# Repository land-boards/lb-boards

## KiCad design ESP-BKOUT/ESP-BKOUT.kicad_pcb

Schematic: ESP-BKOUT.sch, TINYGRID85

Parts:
C1, C3, C4, C5: 0.1uF; R_0805_HandSoldering
C2, C6, C7: 22uF; R_1210_HandSoldering
J1: DCJ0202; JACK_2.1MM
MTG1, MTG2, MTG3, MTG4: CONN_1; MTG-4-40
P1: CONN_01X04; Pin_Header_Straight_1x04
P2: CONN_01X10; Pin_Header_Straight_1x10
P3: CONN_01X08; Pin_Header_Straight_1x08
P4: CONN_01X02; Pin_Header_Straight_1x02
U1: TXS0108; SOG20
U2: AP1117-3.3V; SOT-223
U3: arduino_mini
U4: AZ1117-5.0V; SOT-223
U5: ESP8266-ESP-01

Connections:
+3V3: C5.1, C6.1, U1.2 (VCCA(LV)), U1.10 (OE), U2.2 (VO), U2.4 (VO), U5.3 (CH_PD), U5.7 (3V3)
+5V: C2.1, C3.1, C4.1, C7.1, P1.2, P2.9, P3.7, U1.19 (VCCB(HV)), U2.3 (VIN), U3.12 (5V), U4.2 (VO), U4.4 (VO)
+9V: C1.1, J1.1, U3.15 (Vin), U4.3 (VIN)
/A0: P2.1, U3.4 (A0)
/A1: P2.2, U3.5 (A1)
/A2: P2.3, U3.6 (A2)
/A3: P2.4, U3.7 (A3)
/A6: P2.7, U3.10 (A6)
/A7: P2.8, U3.11 (A7)
/ARDRXD: P1.3, U1.18 (G2), U3.26 (D8)
/ARDTXD: P1.4, U1.20 (B1), U3.27 (#D9)
/D4: P3.4, U3.22 (D4)
/D5: P3.3, U3.23 (#D5)
/D6: P3.2, U3.24 (#D6)
/D7: P3.1, U3.25 (D7)
/ESPRXD: U1.1 (A1), U5.8 (RX)
/ESPTXD: U1.3 (A2), U5.1 (TX)
/SCL: P2.6, U3.9 (A5(SCL))
/SDA: P2.5, U3.8 (A4(SDA))
GND: C1.2, C2.2, C3.2, C4.2, C5.2, C6.2, C7.2, J1.2, J1.3, P1.1, P2.10, P3.8, P4.2, U1.11 (GND), U2.1 (GND), U3.14 (GND), U3.19 (GND), U4.1 (GND), U5.2 (GND)
unnamed: P3.5, U3.21 ((int3)#D3)
unnamed: P3.6, U3.20 ((int2)D2)
unnamed: P4.1, U5.6 (GPIO0)

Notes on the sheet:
VOLTAGE REGULATOR

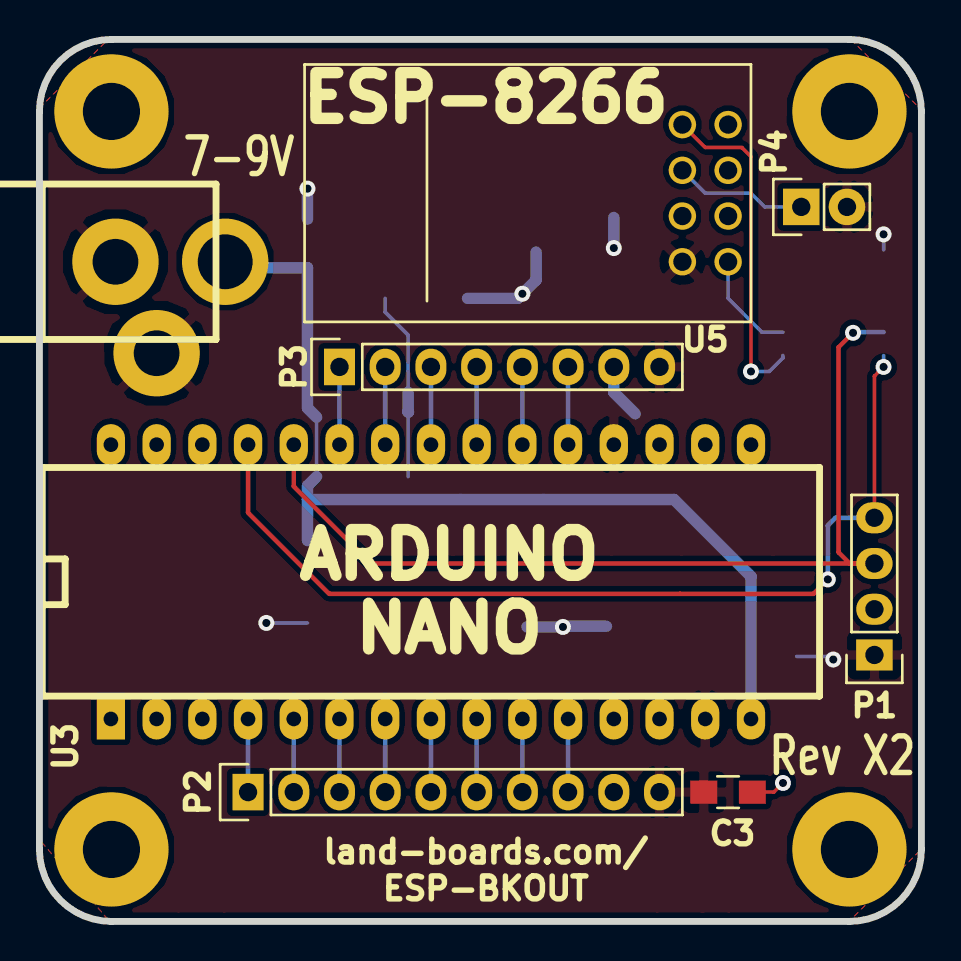
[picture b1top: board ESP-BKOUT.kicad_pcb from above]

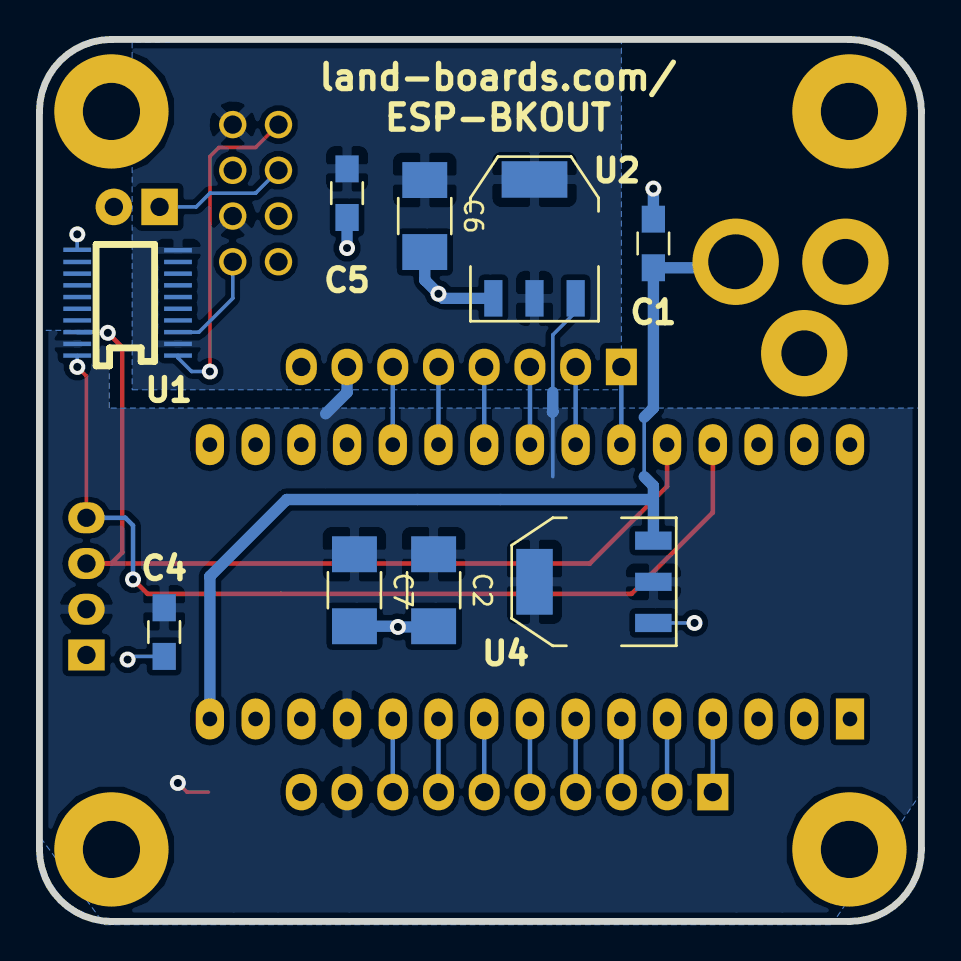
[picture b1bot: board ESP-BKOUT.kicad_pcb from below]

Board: 2 copper layers, 49.0 x 49.0 mm, 21 parts (9 on the bottom side), 23 nets.

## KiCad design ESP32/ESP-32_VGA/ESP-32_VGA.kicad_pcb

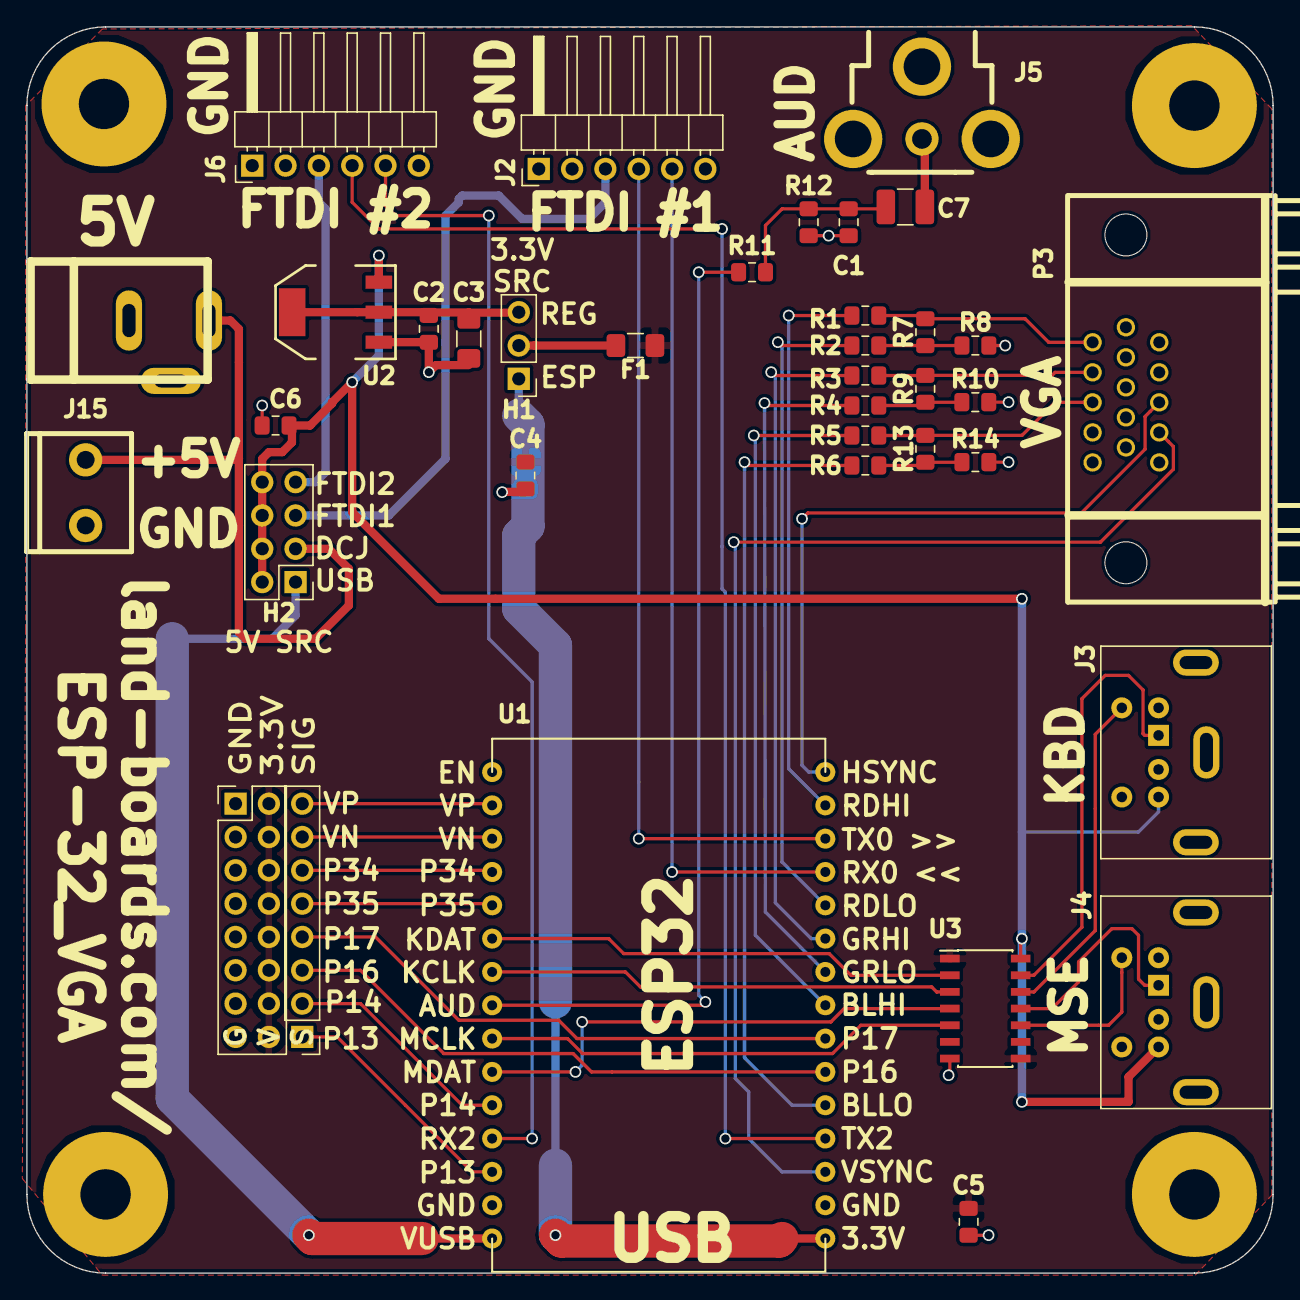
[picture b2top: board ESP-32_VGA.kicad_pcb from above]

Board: 2 copper layers, 95.0 x 95.0 mm, 42 parts (0 on the bottom side), 47 nets.

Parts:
C1, C2, C4, C5, C6: 0.1uF; C_0805_2012Metric_Pad1.15x1.40mm_HandSolder
C3: 10uF; C_1206_3216Metric_Pad1.42x1.75mm_HandSolder
C7: CP1; C_1210_3225Metric_Pad1.42x2.65mm_HandSolder
F1: Polyfuse_Small; Fuse_1206_3216Metric_Pad1.42x1.75mm_HandSolder
H1: Conn_01x03; PinHeader_1x03_P2.54mm_Vertical
H2: Conn_02x04_Odd_Even; PinHeader_2x04_P2.54mm_Vertical
J1: DCJ0202; DCJ-NEW-Slotted
J2, J6: FTDI; PinHeader_1x06_P2.54mm_Horizontal
J3, J4: PS2_DIN6; Connector_Mini-DIN_Female_6Pin_2rows
J5: RCA-JACK; RCA
J15: Conn_01x02; TB2-5MM
MTG1, MTG2, MTG3: MTG_HOLE; MTG-6-32
MTG?1: MTG_HOLE; MTG-6-32
P2: Conn_02x08_Odd_Even; PinHeader_2x08_P2.54mm_Vertical
P3: VGA; DB_15F-VGA-fixed
P4: Conn_01x08; PinHeader_1x08_P2.54mm_Vertical
R1: 1K; R_0805_2012Metric_Pad1.15x1.40mm_HandSolder
R2, R4, R6: 680; R_0805_2012Metric_Pad1.15x1.40mm_HandSolder
R3, R5, R7, R8, R9, R10, R13, R14: 470; R_0805_2012Metric_Pad1.15x1.40mm_HandSolder
R11: 270; R_0805_2012Metric_Pad1.15x1.40mm_HandSolder
R12: 150; R_0805_2012Metric_Pad1.15x1.40mm_HandSolder
TEST1: COUPON; TEST_BLK-REAR
U1: ESP32; ESP32_EXP
U2: AP1117; SOT223
U3: TXS0104; SOIC-14_3.9x8.7mm_P1.27mm

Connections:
+3V3: C4.1, C5.1, F1.1, P2.2, P2.4, P2.6, P2.8, P2.10, P2.12, P2.14, P2.16, U3.1, U3.8
+5V: C6.1, H2.2, H2.4, H2.6, H2.8, J3.4, J4.4, U2.3, U3.14
/AUDIO: R11.2, U1.23
/BLUHI: R5.2, U1.8
/BLULO: R6.2, U1.5
/DCIN: H2.3, J1.1, J15.2
/ESP3V: H1.1, U1.1
/FTDI5V0: H2.5, J2.3
/FTDI5V2: H2.7, J6.3
/GP13: P4.1, U1.28
/GP14: P4.2, U1.26
/GP16: P4.3, U1.6
/GP17: P4.4, U1.7
/GP34: P4.6, U1.19
/GP35: P4.5, U1.20
/GRNHI: R3.2, U1.10
/GRNLO: R4.2, U1.9
/HSYNC: P3.13, U1.15
/KBCLK: U1.22, U3.3
/KBDAT: U1.21, U3.2
/MSECLK: U1.24, U3.5
/MSEDAT: U1.25, U3.4
/REDHI: R1.2, U1.14
/REDLO: R2.2, U1.11
/RX0: J2.5, U1.12
/RX2: J6.5, U1.27
/TX0: J2.4, U1.13
/TX2: J6.4, U1.4
/VN: P4.7, U1.18
/VO3: C2.1, C3.1, H1.3, U2.2, U2.4
/VP: P4.8, U1.17
/VSYNC: P3.14, U1.3
/VUSB: H2.1, U1.30
GND: C1.2, C2.2, C3.2, C4.2, C5.2, C6.2, J1.2, J1.3, J2.1, J3.3, J4.3, J5.1, J5.2, J5.3, J6.1, J15.1, P2.1, P2.3, P2.5, P2.7, P2.9, P2.11, P2.13, P2.15, P3.5, P3.6, P3.7, P3.8, P3.10, R8.1, R10.1, R12.1, R14.1, U1.2, U1.29, U2.1, U3.7
unnamed: C1.1, C7.1, R11.1, R12.2
unnamed: C7.2, J5.4
unnamed: F1.2, H1.2
unnamed: J3.1, U3.13
unnamed: J3.5, U3.12
unnamed: J4.1, U3.11
unnamed: J4.5, U3.10
unnamed: P3.1, R1.1, R7.2
unnamed: P3.2, R3.1, R9.2
unnamed: P3.3, R5.1, R13.2
unnamed: R2.1, R7.1, R8.2
unnamed: R4.1, R9.1, R10.2
unnamed: R6.1, R13.1, R14.2

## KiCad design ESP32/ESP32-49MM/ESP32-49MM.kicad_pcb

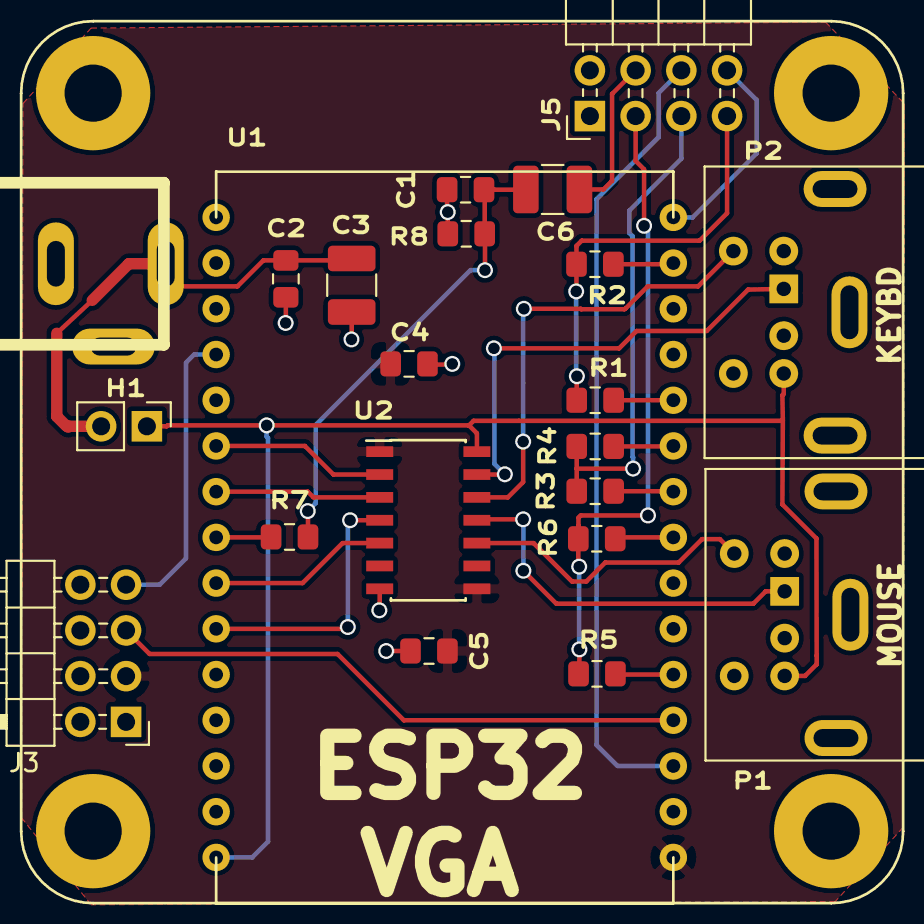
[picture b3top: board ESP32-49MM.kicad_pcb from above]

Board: 2 copper layers, 24 parts (0 on the bottom side), 28 nets.

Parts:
BRD1: COUPON; BD-49X49
C1, C2, C4, C5: 0.1uF; C_0805_2012Metric_Pad1.15x1.40mm_HandSolder
C3, C6: 10uF; C_1210_3225Metric_Pad1.42x2.65mm_HandSolder
H1: Conn_01x02; PinHeader_1x02_P2.54mm_Vertical
J1: DCJ0202; DCJ-NEW-Slotted
J3: Header, Vert, 2x4; PinHeader_2x04_P2.54mm_Horizontal
J5: Conn_02x04_Odd_Even; PinHeader_2x04_P2.54mm_Horizontal
P1: MINI-DIN6, PS2 (GRN); Connector_Mini-DIN_Female_6Pin_2rows
P2: MINI-DIN6, PS2 (PURP); Connector_Mini-DIN_Female_6Pin_2rows
R1, R3, R5: 422; R_0805_2012Metric_Pad1.15x1.40mm_HandSolder
R2, R4, R6: 845; R_0805_2012Metric_Pad1.15x1.40mm_HandSolder
R7: 270; R_0805_2012Metric_Pad1.15x1.40mm_HandSolder
R8: 150; R_0805_2012Metric_Pad1.15x1.40mm_HandSolder
TEST1: COUPON; TEST_BLK-REAR
U1: ESP32 MODULE; ESP32_EXP
U2: TXS0104EDR; SOIC-14_3.9x8.7mm_P1.27mm

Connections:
+3V3: C4.1, C5.1, J3.3, U1.1, U2.1, U2.8
+5V: H1.1, P1.4, P2.4, U1.30, U2.14
/AOUT: C6.2, J5.4
/AUDIO: R7.2, U1.23
/BLUHI: R5.2, U1.5
/BLULO: R6.2, U1.8
/GRNHI: R3.2, U1.9
/GRNLO: R4.2, U1.10
/HSYNC: J5.8, U1.15
/KBCLK: U1.22, U2.3
/KBDAT: U1.21, U2.2
/MSECLK: U1.24, U2.5
/MSEDAT: U1.25, U2.4
/REDHI: R1.2, U1.11
/REDLO: R2.2, U1.14
/RX2: J3.7, U1.19
/TX2: J3.5, U1.4
/VSYNC: J5.6, U1.3
GND: C1.2, C2.2, C3.2, C4.2, C5.2, J1.2, J1.3, J3.1, J5.1, J5.2, P1.3, P2.3, R8.1, U1.2, U1.29, U2.7
unnamed: C1.1, C6.1, R7.1, R8.2
unnamed: C2.1, C3.1, H1.2, J1.1
unnamed: J5.3, R5.1, R6.1
unnamed: J5.5, R3.1, R4.1
unnamed: J5.7, R1.1, R2.1
unnamed: P1.1, U2.11
unnamed: P1.5, U2.10
unnamed: P2.1, U2.13
unnamed: P2.5, U2.12

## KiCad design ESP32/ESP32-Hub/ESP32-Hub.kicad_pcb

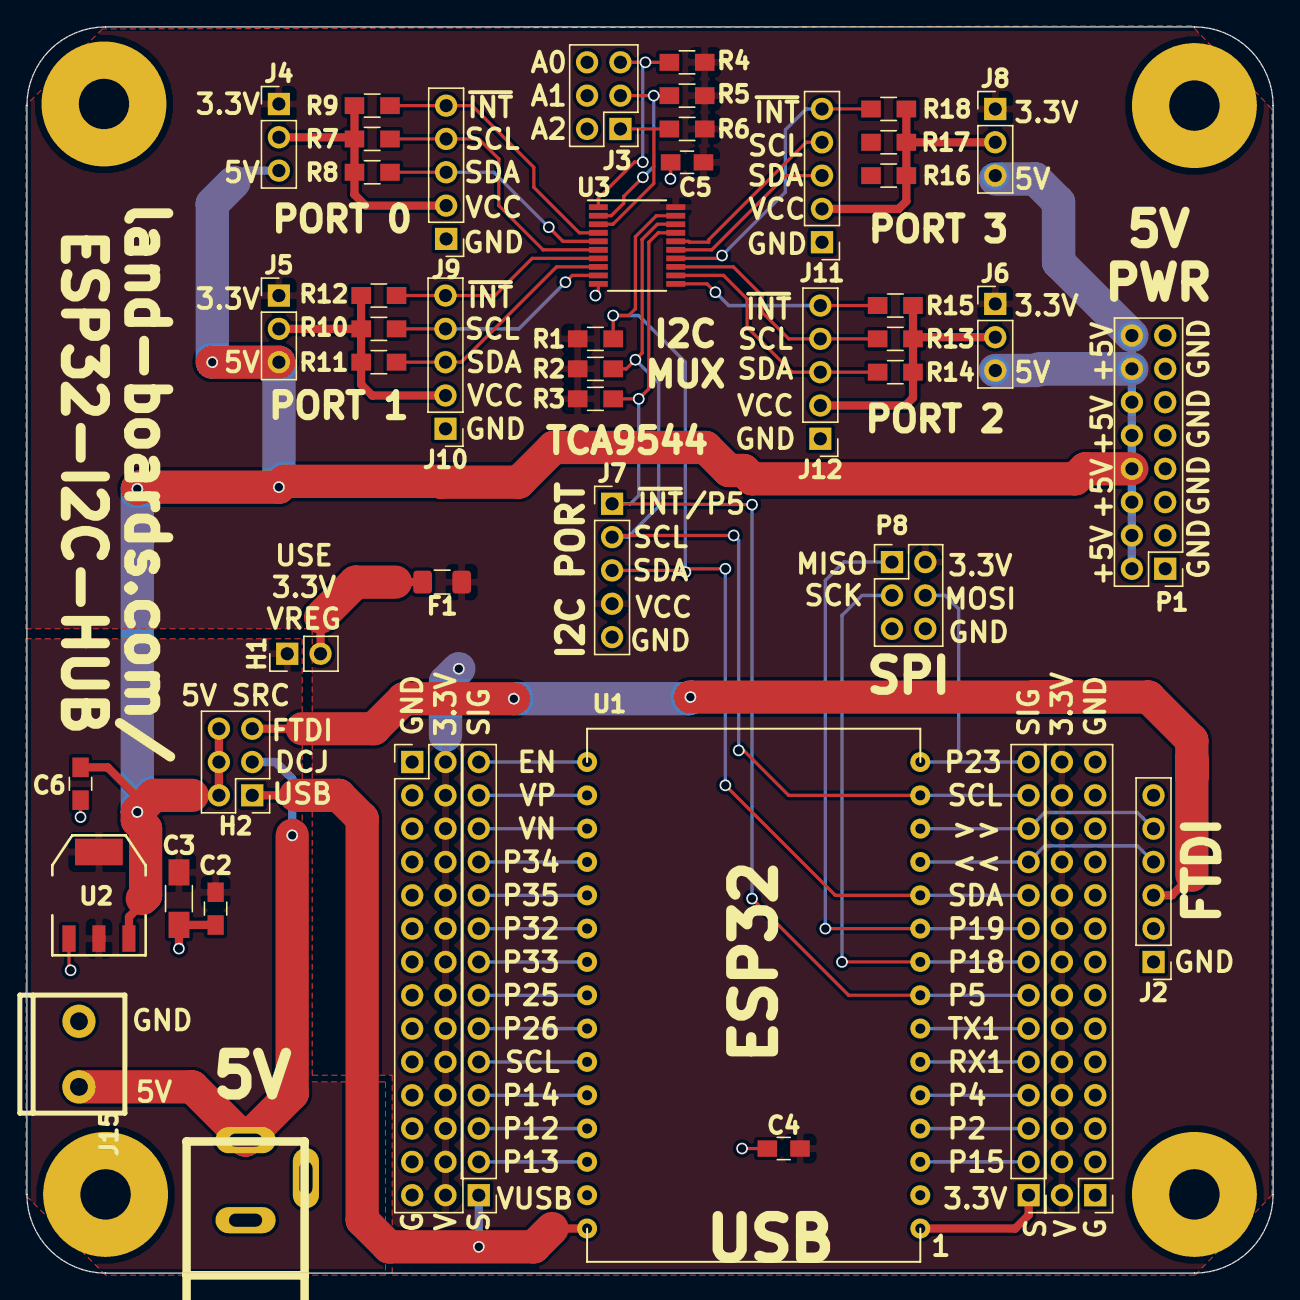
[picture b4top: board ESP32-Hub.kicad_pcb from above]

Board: 2 copper layers, 95.0 x 95.0 mm, 52 parts (0 on the bottom side), 54 nets.

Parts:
C2, C4, C5, C6: 0.1uF; C_0805_HandSoldering
C3: 10uF; C_1206_HandSoldering
F1: Polyfuse, 1A (1206); Fuse_1206_3216Metric_Pad1.42x1.75mm_HandSolder
H1: Header, Rt ang, 1x2; PinHeader_1x02_P2.54mm_Vertical
H2: Header, Vert, 2x3; PinHeader_2x03_P2.54mm_Vertical
J1: DC Pwr Jack, 5.5mmx2.1mm; DCJ-NEW-Slotted
J2: Header, 1x6, Rt Ang, (FTDI); Pin_Header_Straight_1x06_Pitch2.54mm
J3: Header, Vert, 2x3; Pin_Header_Straight_2x03_Pitch2.54mm
J4, J5, J6, J8: Header, Strt, 1x3; Pin_Header_Straight_1x03_Pitch2.54mm
J7, J9, J10, J11, J12: Header, Strt, 1x5; Pin_Header_Straight_1x05_Pitch2.54mm
J15: Term Blk, 5mm, 1x2; TB2-5MM
MTG1, MTG2, MTG3, MTG4: MTG_HOLE; MTG-6-32
P1: Header, Vert, 2x8; Pin_Header_Straight_2x08_Pitch2.54mm
P2, P11: Header, Vert, 2x14; Pin_Header_Straight_2x14_Pitch2.54mm
P8: Header, Vert, 2x3; Pin_Header_Straight_2x03_Pitch2.54mm
P12, P13: Header, Vert, 1x14; Pin_Header_Straight_1x14_Pitch2.54mm
R1, R3, R7, R8, R10, R11, R13, R14, R16, R17: 2.2K; R_0805_HandSoldering
R2, R4, R5, R6, R9, R12, R15, R18: 10K; R_0805_HandSoldering
U1: ESP32 MODULE; ESP32_EXP
U2: AP1117E33G-13 (3.3V); SOT223
U3: PCA9544APWR; TSSOP-20_4.4x6.5mm_Pitch0.65mm

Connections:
+3V3: C4.1, C5.1, F1.1, J4.1, J5.1, J6.1, J7.4, J8.1, P2.2, P2.4, P2.6, P2.8, P2.10, P2.12, P2.14, P2.16, P2.18, P2.20, P2.22, P2.24, P2.26, P2.28, P8.2, P11.2, P11.4, P11.6, P11.8, P11.10, P11.12, P11.14, P11.16, P11.18, P11.20, P11.22, P11.24, P11.26, P11.28, R1.1, R2.1, R3.1, R4.1, R5.1, R6.1, U3.20
+5V: C6.1, H2.2, H2.4, H2.6, J4.3, J5.3, J6.3, J8.3, P1.2, P1.4, P1.6, P1.8, P1.10, P1.12, P1.14, P1.16, U2.3
/A0: J3.5, R4.2, U3.1
/A1: J3.3, R5.2, U3.2
/A2: J3.1, R6.2, U3.3
/DCIN: H2.3, J1.1, J15.1
/EN: P13.14, U1.16
/FTDI5V: H2.5, J2.3
/GP2: P12.3, U1.4
/GP4: P12.4, U1.5
/GP5: J7.1, P12.7, R3.2, U1.8, U3.17
/GP12: P13.3, U1.27
/GP13: P13.2, U1.28
/GP14: P13.4, U1.26
/GP15: P12.2, U1.3
/GP18: P8.3, P12.8, U1.9
/GP19: P8.1, P12.9, U1.10
/GP23: P8.4, P12.14, U1.15
/GP25: P13.7, U1.23
/GP26: P13.6, U1.24
/GP27: P13.5, U1.25
/GP32: P13.9, U1.21
/GP33: P13.8, U1.22
/GP34: P13.11, U1.19
/GP35: P13.10, U1.20
/INT0: J9.5, R9.2, U3.4
/INT1: J10.5, R12.2, U3.7
/INT2: J12.5, R15.2, U3.11
/INT3: J11.5, R18.2, U3.14
/RX0: J2.4, P12.11, U1.12
/RX2: P12.5, U1.6
/SC0: J9.4, R7.2, U3.6
/SC1: J10.4, R10.2, U3.9
/SC2: J12.4, R13.2, U3.13
/SC3: J11.4, U3.16
/SD0: J9.3, R8.2, U3.5
/SD1: J10.3, R11.2, U3.8
/SD2: J12.3, R14.2, U3.12
/SD3: J11.3, U3.15
/STM_SCL: J7.2, P12.13, R2.2, U1.14, U3.18
/STM_SDA: J7.3, P12.10, R1.2, U1.11, U3.19
/TX0: J2.5, P12.12, U1.13
/TX2: P12.6, U1.7
/VN: P13.12, U1.18
/VO3: C2.1, C3.1, H1.1, U2.2, U2.4
/VP: P13.13, U1.17
/VUSB: H2.1, P13.1, U1.30
GND: C2.2, C3.2, C4.2, C5.2, C6.2, J1.2, J1.3, J2.1, J3.2, J3.4, J3.6, J7.5, J9.1, J10.1, J11.1, J12.1, J15.2, P1.1, P1.3, P1.5, P1.7, P1.9, P1.11, P1.13, P1.15, P2.1, P2.3, P2.5, P2.7, P2.9, P2.11, P2.13, P2.15, P2.17, P2.19, P2.21, P2.23, P2.25, P2.27, P8.6, P11.1, P11.3, P11.5, P11.7, P11.9, P11.11, P11.13, P11.15, P11.17, P11.19, P11.21, P11.23, P11.25, P11.27, U1.2, U1.29, U2.1, U3.10
unnamed: F1.2, H1.2
unnamed: J4.2, J9.2, R7.1, R8.1, R9.1
unnamed: J5.2, J10.2, R10.1, R11.1, R12.1
unnamed: J8.2, J11.2, R16.1, R17.1, R18.1
unnamed: J6.2, J12.2, R13.1, R14.1, R15.1
unnamed: P12.1, U1.1

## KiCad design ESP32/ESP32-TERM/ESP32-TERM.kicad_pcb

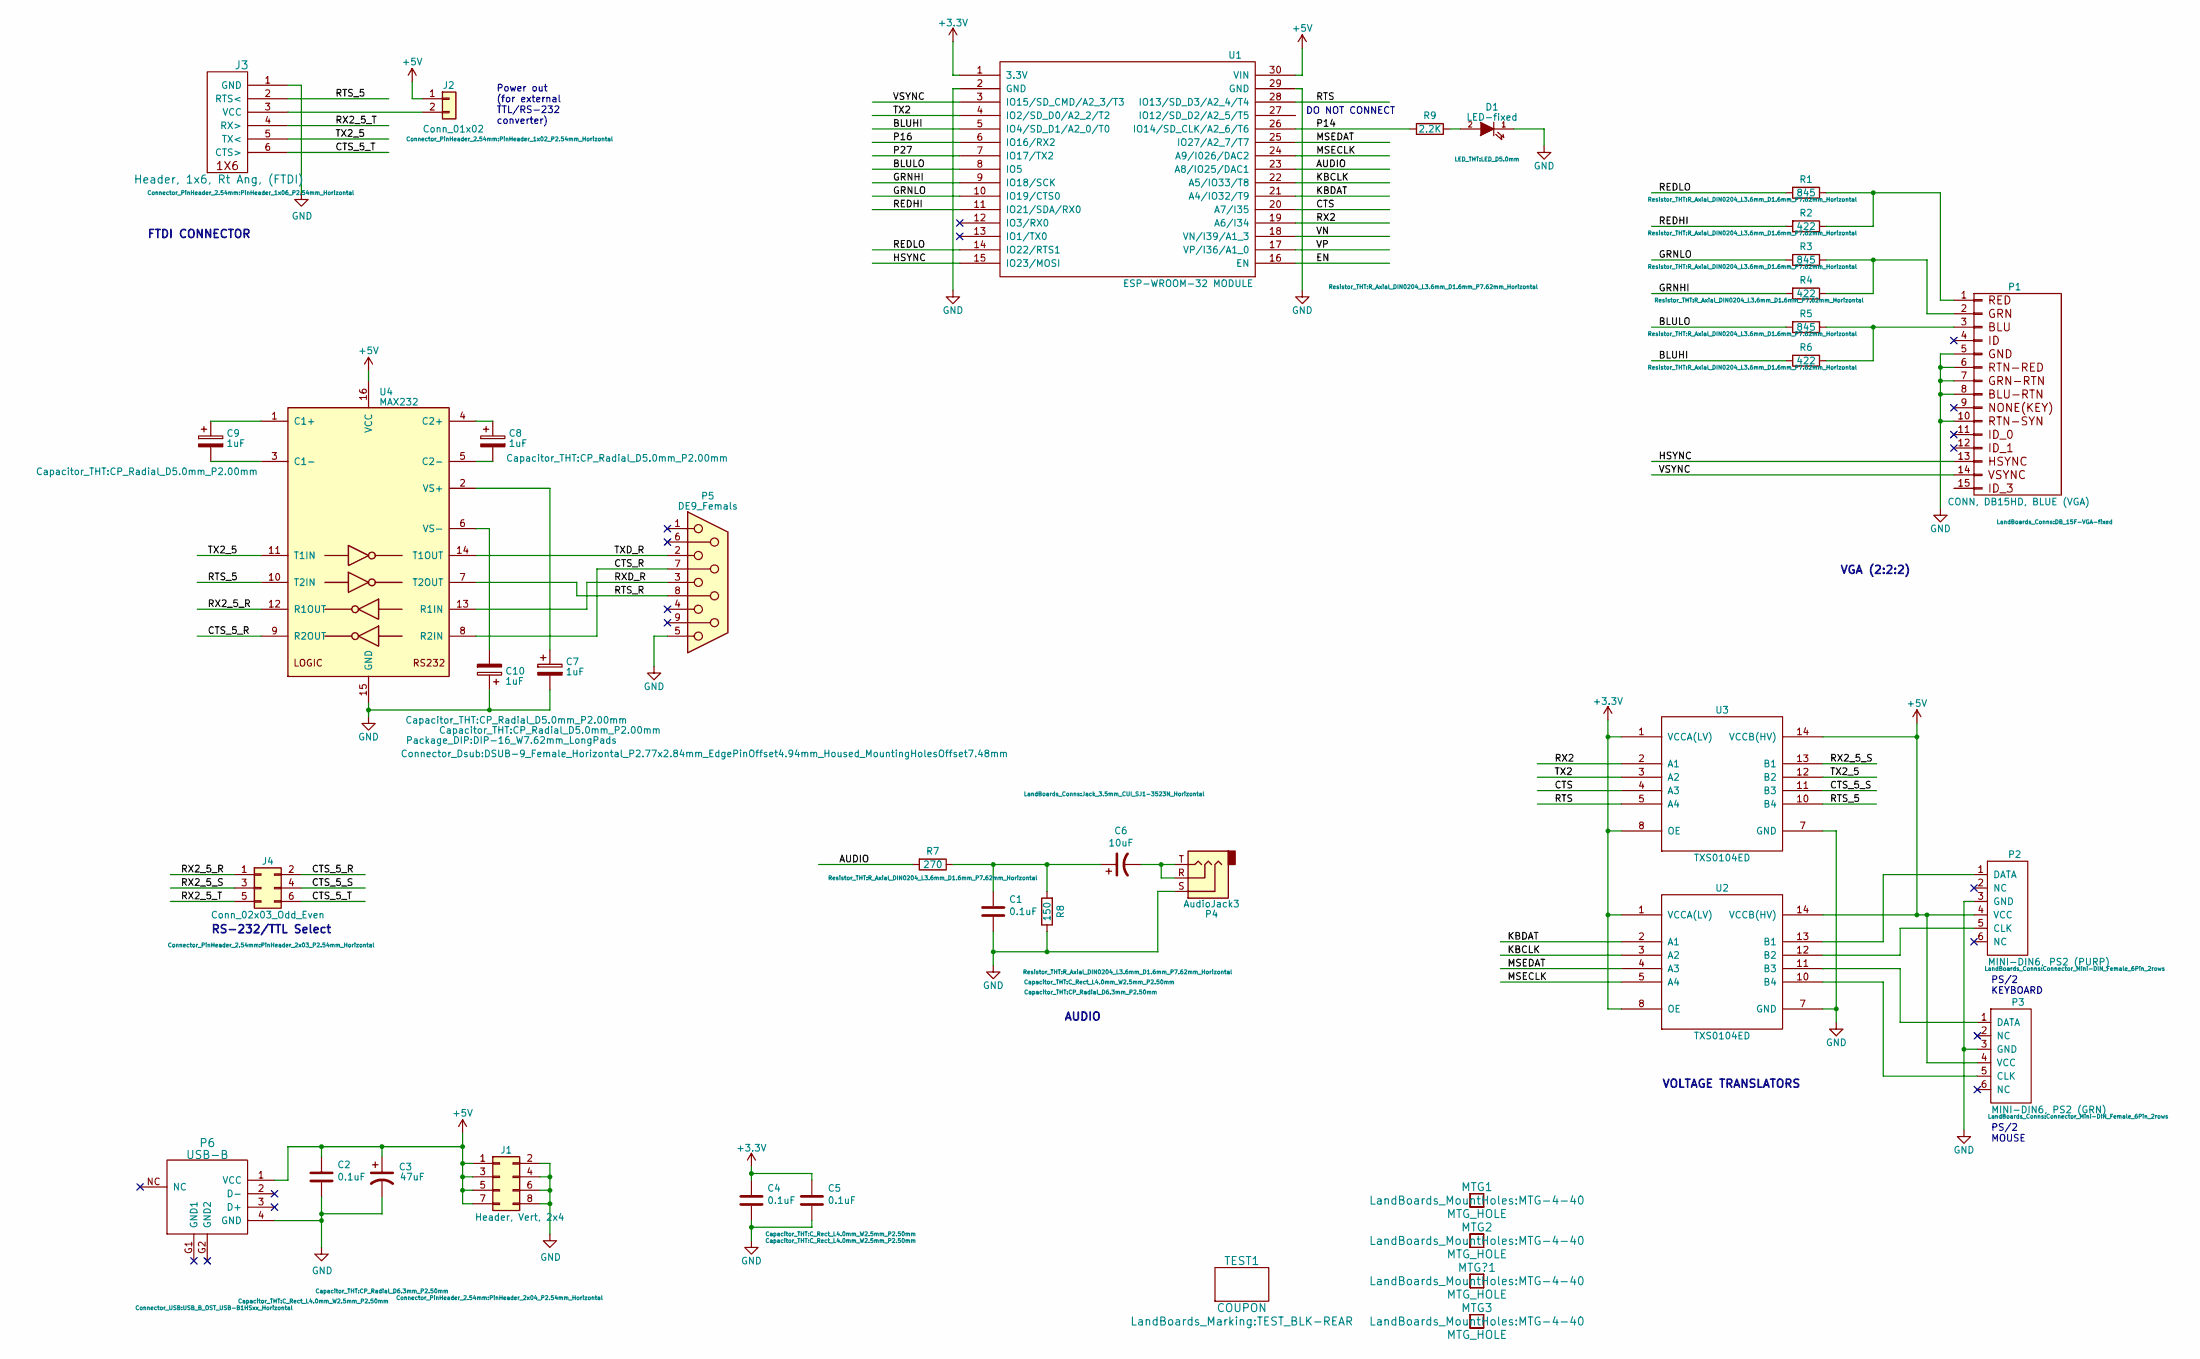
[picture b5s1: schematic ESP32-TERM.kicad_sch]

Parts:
C1, C2, C4, C5: 0.1uF; C_Rect_L4.0mm_W2.5mm_P2.50mm
C3: 47uF; CP_Radial_D6.3mm_P2.50mm
C6: 10uF; CP_Radial_D6.3mm_P2.50mm
C7, C8, C9, C10: 1uF; CP_Radial_D5.0mm_P2.00mm
D1: LED-fixed; LED_D5.0mm
J1: Header, Vert, 2x4; PinHeader_2x04_P2.54mm_Horizontal
J2: Conn_01x02; PinHeader_1x02_P2.54mm_Horizontal
J3: Header, 1x6, Rt Ang, (FTDI); PinHeader_1x06_P2.54mm_Horizontal
J4: Conn_02x03_Odd_Even; PinHeader_2x03_P2.54mm_Horizontal
MTG1, MTG2, MTG3: MTG_HOLE; MTG-4-40
MTG?1: MTG_HOLE; MTG-4-40
P1: CONN, DB15HD, BLUE (VGA); DB_15F-VGA-fixed
P2: MINI-DIN6, PS2 (PURP); Connector_Mini-DIN_Female_6Pin_2rows
P3: MINI-DIN6, PS2 (GRN); Connector_Mini-DIN_Female_6Pin_2rows
P4: AudioJack3; Jack_3.5mm_CUI_SJ1-3523N_Horizontal
P5: DE9_Femals; DSUB-9_Female_Horizontal_P2.77x2.84mm_EdgePinOffset4.94mm_H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
P6: USB-B; USB_B_OST_USB-B1HSxx_Horizontal
R1, R3, R5: 845; R_Axial_DIN0204_L3.6mm_D1.6mm_P7.62mm_Horizontal
R2, R4, R6: 422; R_Axial_DIN0204_L3.6mm_D1.6mm_P7.62mm_Horizontal
R7: 270; R_Axial_DIN0204_L3.6mm_D1.6mm_P7.62mm_Horizontal
R8: 150; R_Axial_DIN0204_L3.6mm_D1.6mm_P7.62mm_Horizontal
R9: 2.2K; R_Axial_DIN0204_L3.6mm_D1.6mm_P7.62mm_Horizontal
TEST1: COUPON; TEST_BLK-REAR
U1: ESP-WROOM-32 MODULE; ESP32_EXP
U2, U3: TXS0104ED; SOIC-14_3.9x8.7mm_P1.27mm
U4: MAX232; DIP-16_W7.62mm_LongPads

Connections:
+3V3: C4.1, C5.1, U1.1 (3.3V), U2.1 (VCCA(LV)), U2.8 (OE), U3.1 (VCCA(LV)), U3.8 (OE)
+5V: C2.1, C3.1, J1.1, J1.3, J1.5, J1.7, J2.1, P2.4 (VCC), P3.4 (VCC), P6.1 (VCC), U1.30 (VIN), U2.14 (VCCB(HV)), U3.14 (VCCB(HV)), U4.16 (VCC)
/AUDIO: R7.2, U1.23 (A8/IO25/DAC1)
/BLUHI: R6.2, U1.5 (IO4/SD_D1/A2_0/T0)
/BLULO: R5.2, U1.8 (IO5)
/CTS: U1.20 (A7/I35), U3.4 (A3)
/CTS_5_R: J4.2, U4.9 (R2OUT)
/CTS_5_S: J4.4, U3.11 (B3)
/CTS_5_T: J3.6 (CTS>), J4.6
/CTS_R: P5.7, U4.8 (R2IN)
/EN: U1.16 (EN)
/GRNHI: R4.2, U1.9 (IO18/SCK)
/GRNLO: R3.2, U1.10 (IO19/CTS0)
/HSYNC: P1.13, U1.15 (IO23/MOSI)
/KBCLK: U1.22 (A5/IO33/T8), U2.3 (A2)
/KBDAT: U1.21 (A4/IO32/T9), U2.2 (A1)
/MSECLK: U1.24 (A9/I026/DAC2), U2.5 (A4)
/MSEDAT: U1.25 (IO27/A2_7/T7), U2.4 (A3)
/P14: R9.2, U1.26 (IO14/SD_CLK/A2_6/T6)
/P16: U1.6 (IO16/RX2)
/P27: U1.7 (IO17/TX2)
/REDHI: R2.2, U1.11 (IO21/SDA/RX0)
/REDLO: R1.2, U1.14 (IO22/RTS1)
/RTS: U1.28 (IO13/SD_D3/A2_4/T4), U3.5 (A4)
/RTS_5: J3.2 (RTS<), U3.10 (B4), U4.10 (T2IN)
/RTS_R: P5.8, U4.7 (T2OUT)
/RX2: U1.19 (A6/I34), U3.2 (A1)
/RX2_5_R: J4.1, U4.12 (R1OUT)
/RX2_5_S: J4.3, U3.13 (B1)
/RX2_5_T: J3.4 (RX>), J4.5
/RXD_R: P5.3, U4.13 (R1IN)
/TX2: U1.4 (IO2/SD_D0/A2_2/T2), U3.3 (A2)
/TX2_5: J3.5 (TX<), U3.12 (B2), U4.11 (T1IN)
/TXD_R: P5.2, U4.14 (T1OUT)
/VN: U1.18 (VN/I39/A1_3)
/VP: U1.17 (VP/I36/A1_0)
/VSYNC: P1.14, U1.3 (IO15/SD_CMD/A2_3/T3)
GND: C1.2, C2.2, C3.2, C4.2, C5.2, C7.2, C10.1, D1.1 (K), J1.2, J1.4, J1.6, J1.8, J3.1 (GND), P1.5, P1.6, P1.7, P1.8, P1.10, P2.3 (GND), P3.3 (GND), P4.S, P5.5, P6.4 (GND), R8.1, U1.2 (GND), U1.29 (GND), U2.7 (GND), U3.7 (GND), U4.15 (GND)
unnamed: C1.1, C6.1, R7.1, R8.2
unnamed: C6.2, P4.R, P4.T
unnamed: D1.2 (A), R9.1
unnamed: J2.2, J3.3 (VCC)
unnamed: P1.1, R1.1, R2.1
unnamed: P1.2, R3.1, R4.1
unnamed: P1.3, R5.1, R6.1
unnamed: P2.5 (CLK), U2.12 (B2)
unnamed: P2.1 (DATA), U2.13 (B1)
unnamed: P3.5 (CLK), U2.10 (B4)
unnamed: P3.1 (DATA), U2.11 (B3)
unnamed: C9.1, U4.1 (C1+)
unnamed: C9.2, U4.3 (C1-)
unnamed: C8.1, U4.4 (C2+)
unnamed: C8.2, U4.5 (C2-)
unnamed: C7.1, U4.2 (VS+)
unnamed: C10.2, U4.6 (VS-)

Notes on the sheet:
VOLTAGE TRANSLATORS
AUDIO
Power out (for external TTL/RS-232 converter)
PS/2 KEYBOARD
DO NOT CONNECT
VGA (2:2:2)
PS/2 MOUSE
FTDI CONNECTOR
RS-232/TTL Select

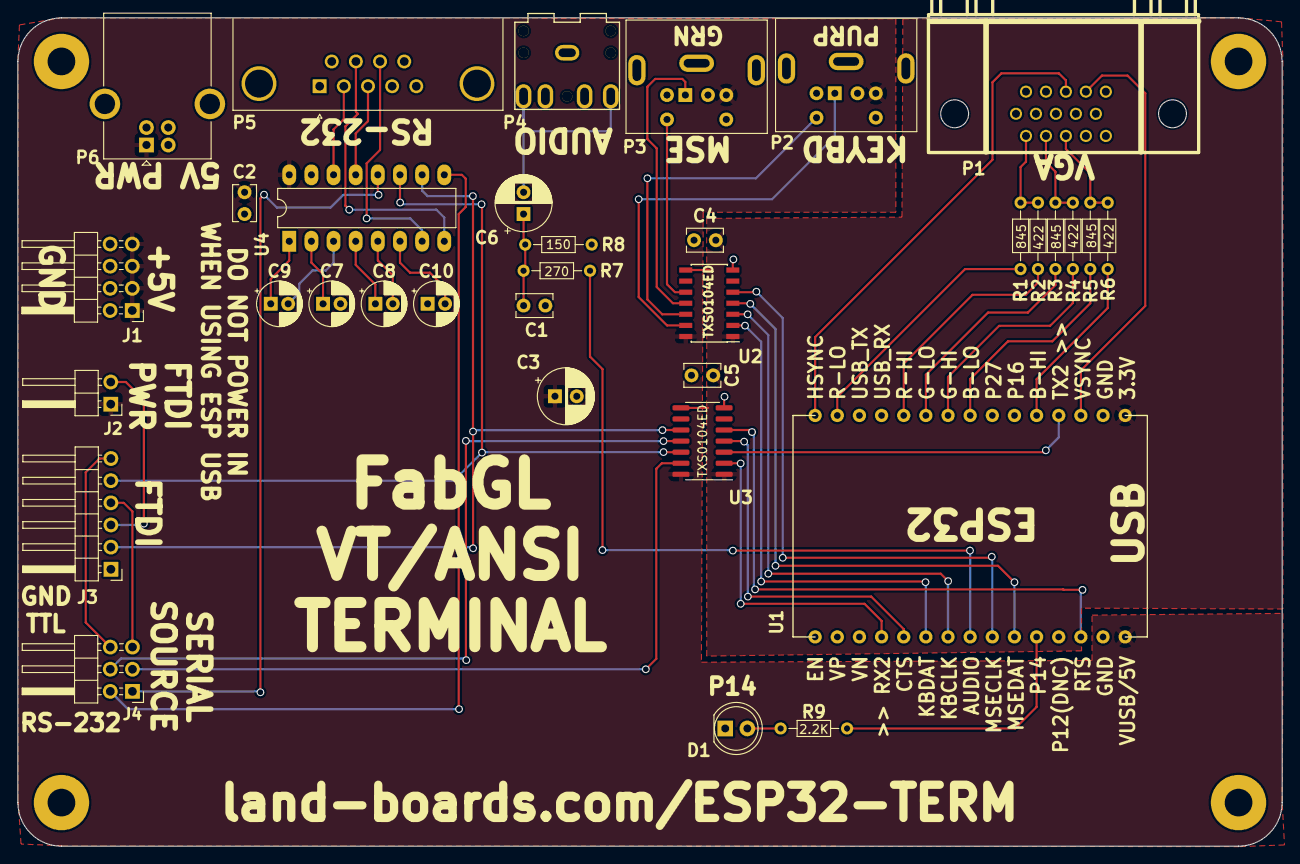
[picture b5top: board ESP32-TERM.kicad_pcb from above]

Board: 2 copper layers, 145.0 x 95.0 mm, 39 parts (0 on the bottom side), 50 nets.

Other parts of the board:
TEST: COUPON; TEST_BLK-REAR
